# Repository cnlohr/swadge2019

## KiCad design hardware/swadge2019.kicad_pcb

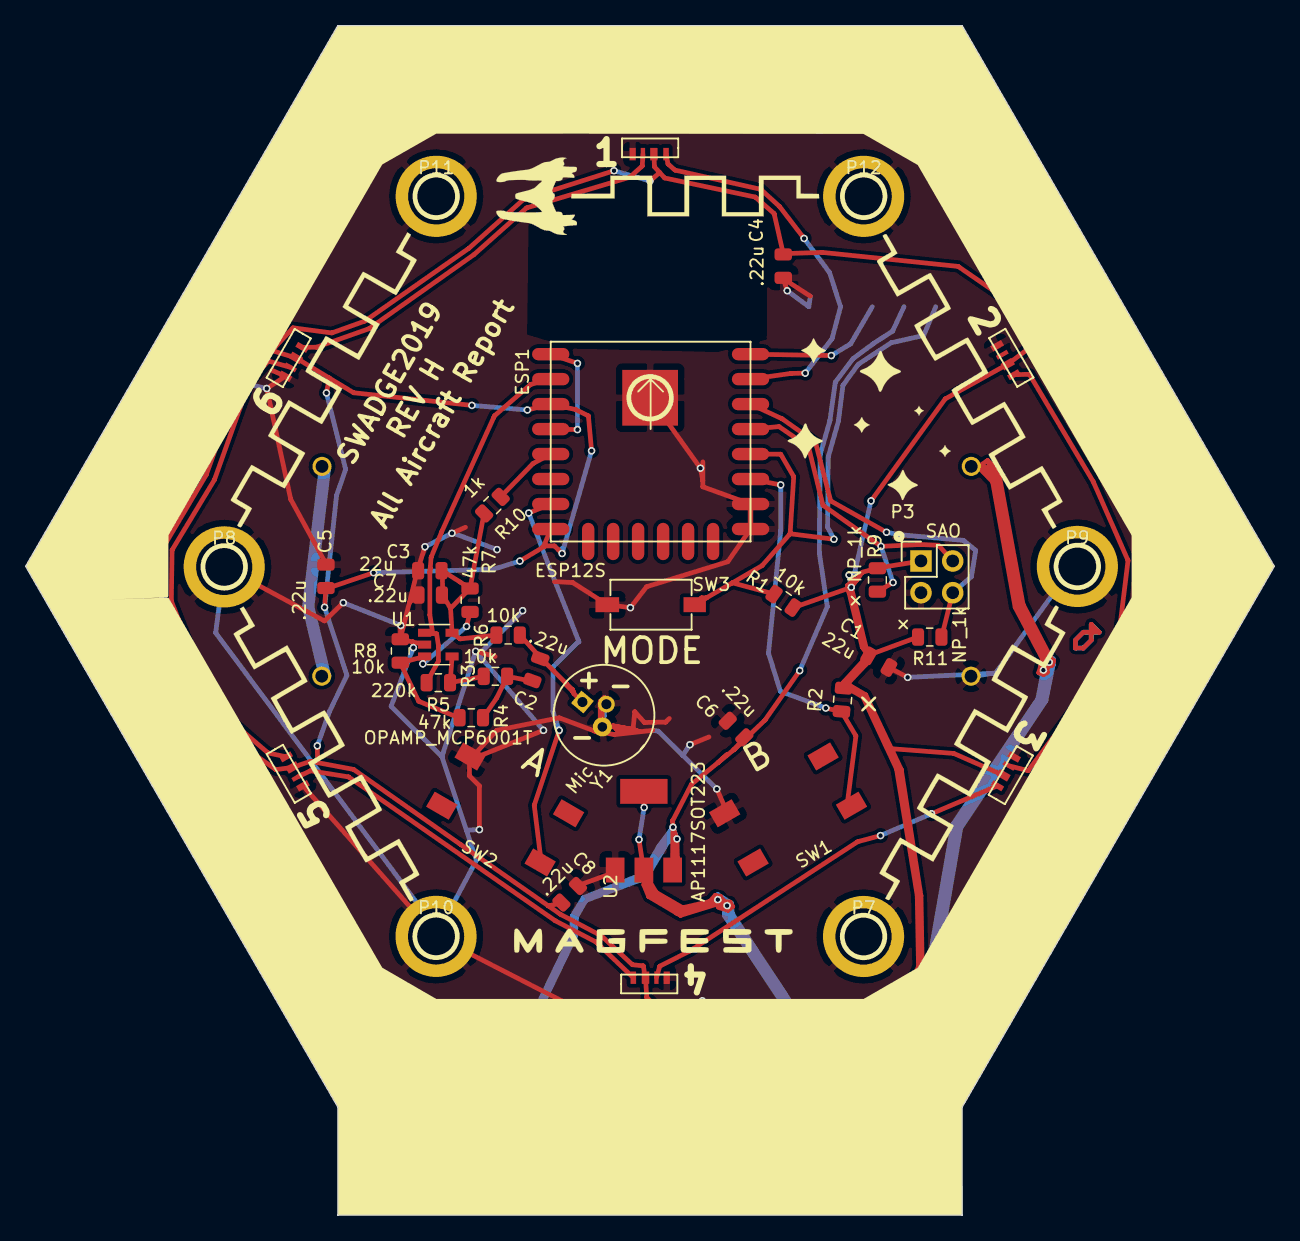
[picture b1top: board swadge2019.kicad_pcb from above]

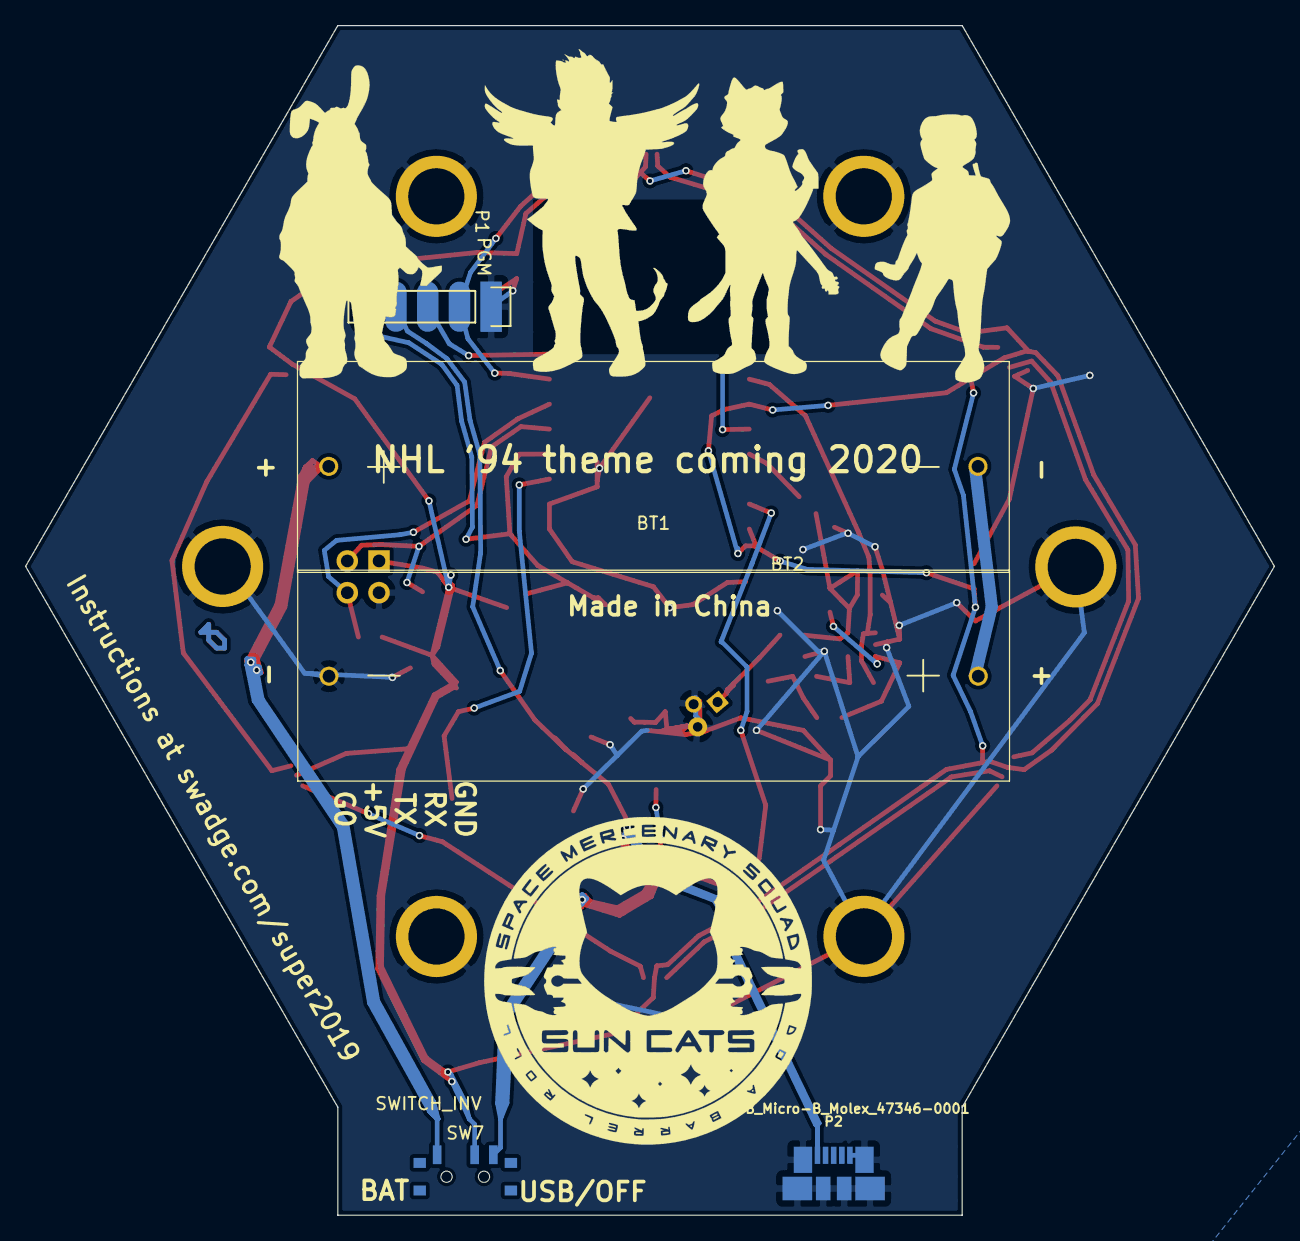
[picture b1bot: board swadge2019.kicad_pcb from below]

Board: 2 copper layers, 100.0 x 95.3 mm, 46 parts (5 on the bottom side), 26 nets.

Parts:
BT1, BT2: Battery; 2460
C1, C3: 22u; C_0805_2012Metric
C2, C4, C5, C6, C7, C8: .22u; C_0805_2012Metric
D1, D2, D3, D4, D5, D6: SK6812SIDE
ESP1: ESP12S; ESP12E
P1: PGM; Pin_Header_Straight_1x05
P2: USB_Micro-B_Molex_47346-0001
P3: SAO; Pin_Header_Straight_2x02
P5: LOGO
P7, P8, P9, P10, P11, P12, P13: CONN_1; 632HOLE
R1, R3, R6, R8: 10k; R_0805_2012Metric
R2: NOPOP-internal?; R_0805_2012Metric
R4, R7: 47k; R_0805_2012Metric
R5: 220k; R_0805_2012Metric
R9, R11: NP_1k; R_0805_2012Metric
R10: 1k; R_0805_2012Metric
SW1: B; SW_4-1437565-2
SW2: A; SW_4-1437565-2
SW3: MODE; TACT_3x6_SINGLE
SW7: SWITCH_INV; SW_SPDT_PCM12
U1: OPAMP_MCP6001T; SOT-23-5
U2: AP1117SOT223; SOT-223-3_TabPin2
Y1: Mic; C_Radial_D8_L13_P3.8

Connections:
+3V3: C1.1, C4.1, C5.1, C8.1, D1.2, D2.2, D3.2, D4.2, D5.2, D6.2, ESP1.3, ESP1.8, P3.1, R1.1, R2.1, R9.1, R11.1, SW7.2
+5V: C6.1, P1.4, P2.1, U2.3
ADCPIN: ESP1.2, R5.1, U1.1
AUDPWR: C3.1, C7.1, R6.1, R7.1, R10.2, U1.5
GND: BT2.2, C1.2, C3.2, C4.2, C5.2, C6.2, C7.2, C8.2, D1.4, D2.4, D3.4, D4.4, D5.4, D6.4, ESP1.15, ESP1.16, P1.1, P2.5, P2.6, P3.3, P7.1, P8.1, P9.1, P10.1, P11.1, P12.1, P13.1, R8.2, SW1.4, SW2.4, SW3.2, U1.2, U2.1, Y1.2
GPIO0: ESP1.18, P1.5, R1.2, SW3.1
GPIO2: ESP1.17, R2.2, SW1.1
GPIO4: ESP1.19, P3.2, R9.2
GPIO5: ESP1.20, P3.4, R11.2
GPIO13: ESP1.7, SW2.1
unnamed: BT1.1, SW7.1
unnamed: BT1.2, BT2.1
unnamed: C2.1, R3.2, R4.2
unnamed: C2.2, R6.2, Y1.1
unnamed: D1.3, D2.1
unnamed: D2.3, D3.1
unnamed: D3.3, D4.1
unnamed: D4.3, D5.1
unnamed: D5.3, D6.1
unnamed: ESP1.1, ESP1.4
unnamed: ESP1.5, R10.1
unnamed: R3.1, R5.2, U1.4
unnamed: SW7.3, U2.2
RX: D1.1, ESP1.21, P1.2
TX: ESP1.22, P1.3
VGS: R4.1, R7.2, R8.1, U1.3

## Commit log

2020-11-11 Rescued schematic, started adding 3D models to layout
2020-11-11 Added missing stuff
2020-11-11 Updated switch and usb models
2020-11-11 Added donut diffuser
2020-11-11 Properly sized TACT_3x6_SINGLE model
2020-11-12 Added cube for LEDs
